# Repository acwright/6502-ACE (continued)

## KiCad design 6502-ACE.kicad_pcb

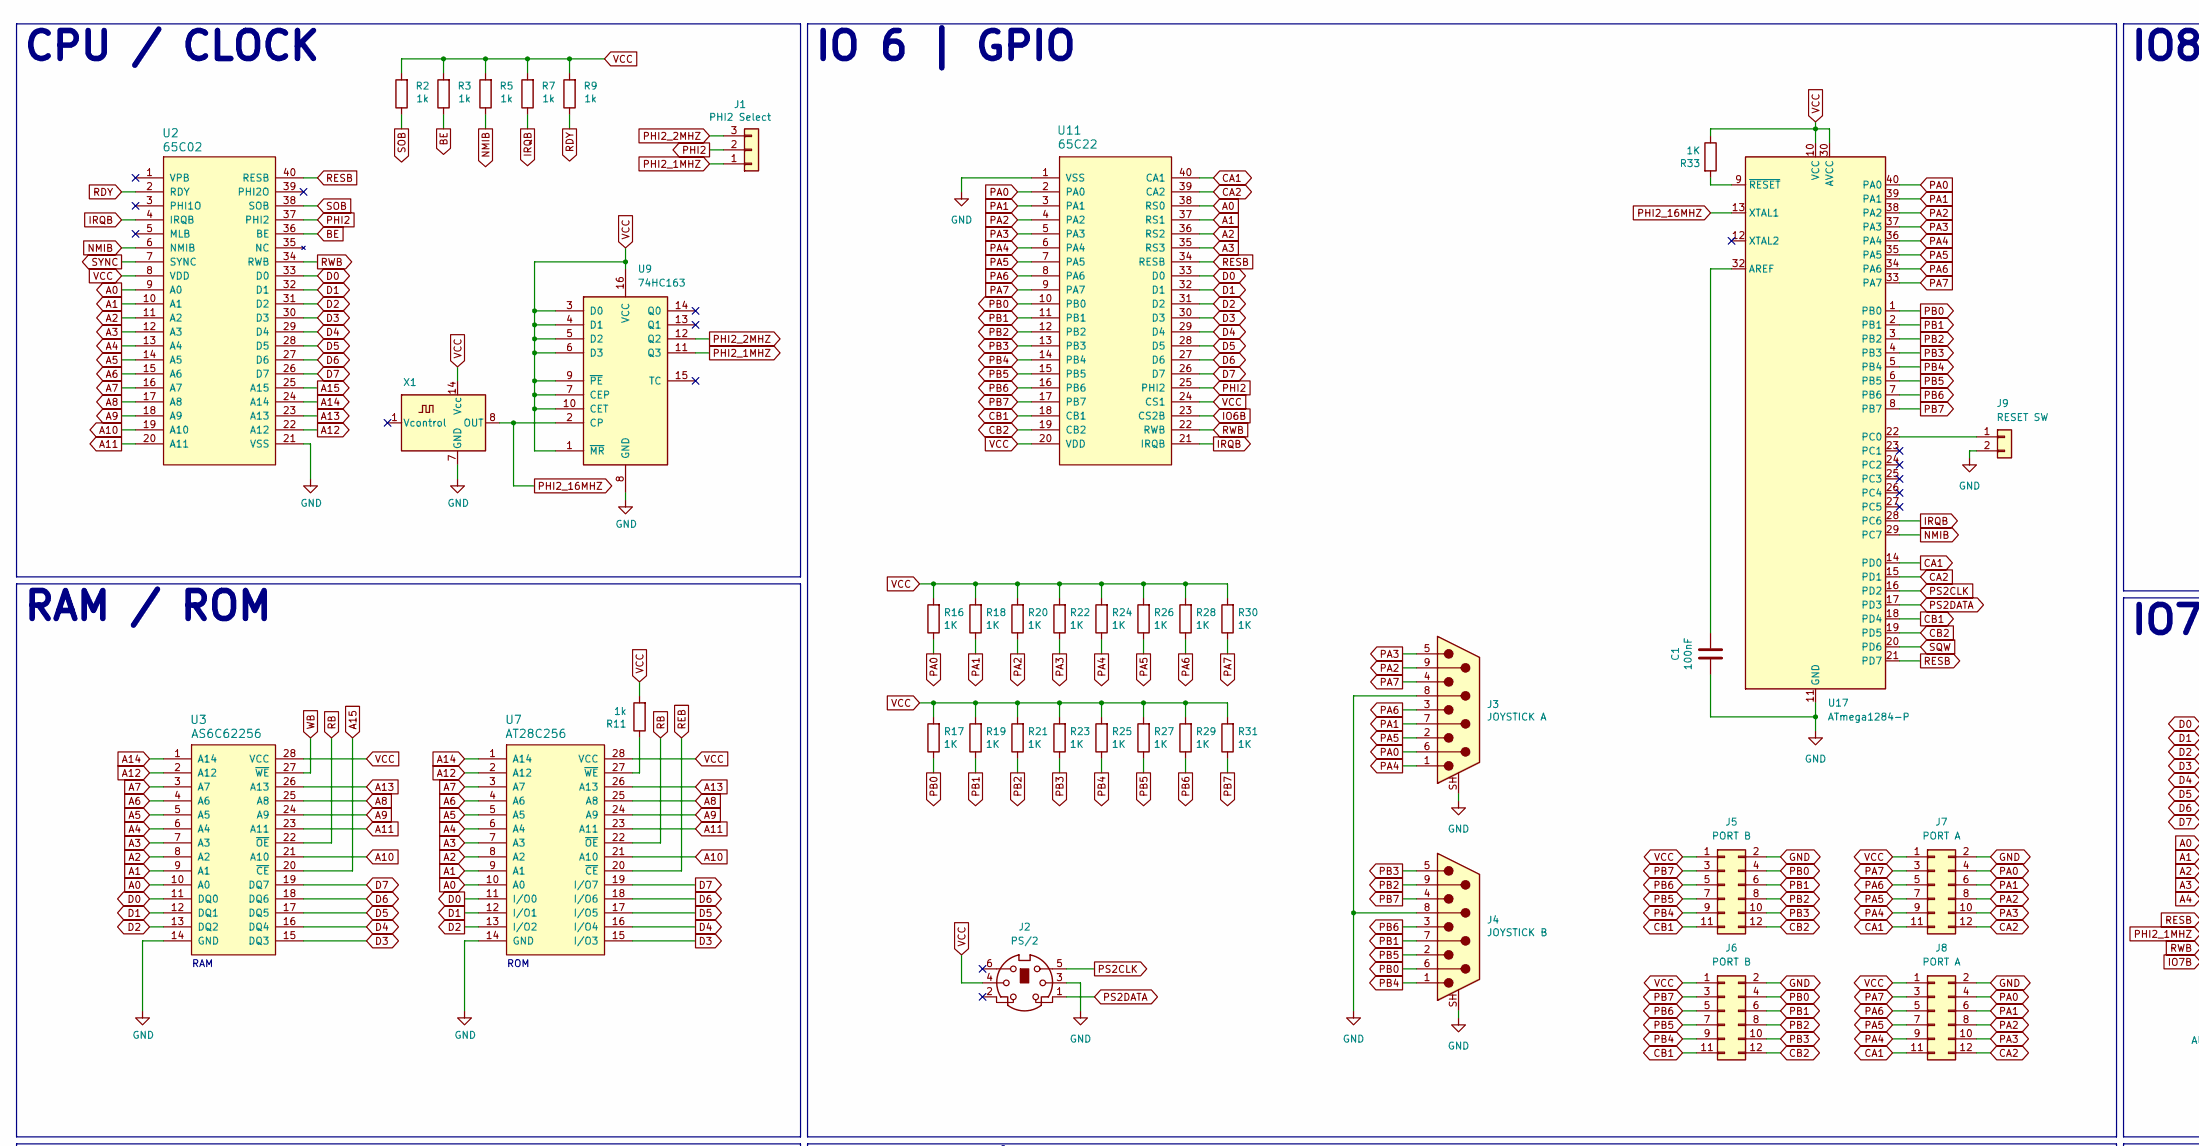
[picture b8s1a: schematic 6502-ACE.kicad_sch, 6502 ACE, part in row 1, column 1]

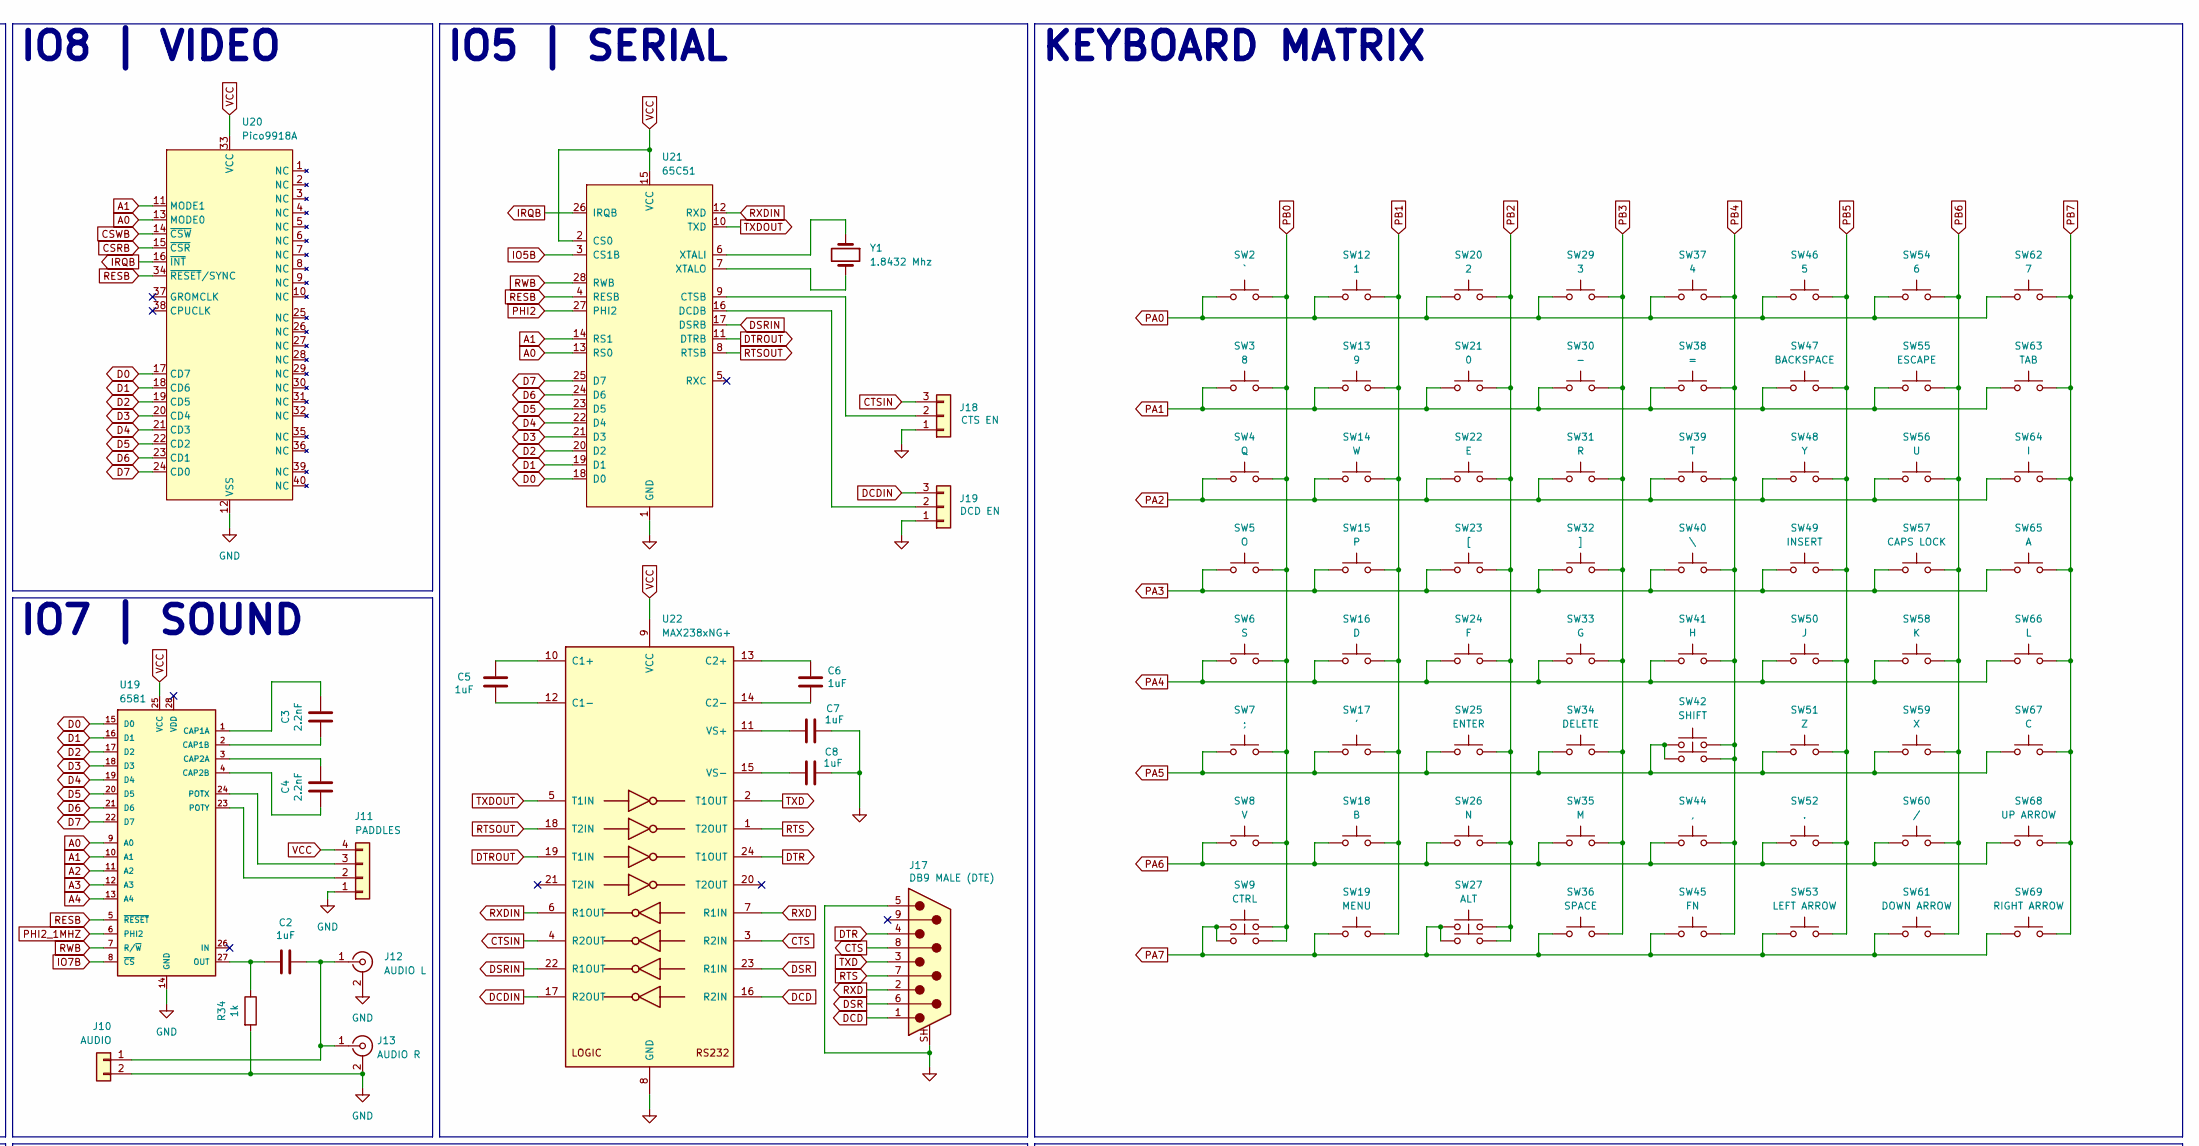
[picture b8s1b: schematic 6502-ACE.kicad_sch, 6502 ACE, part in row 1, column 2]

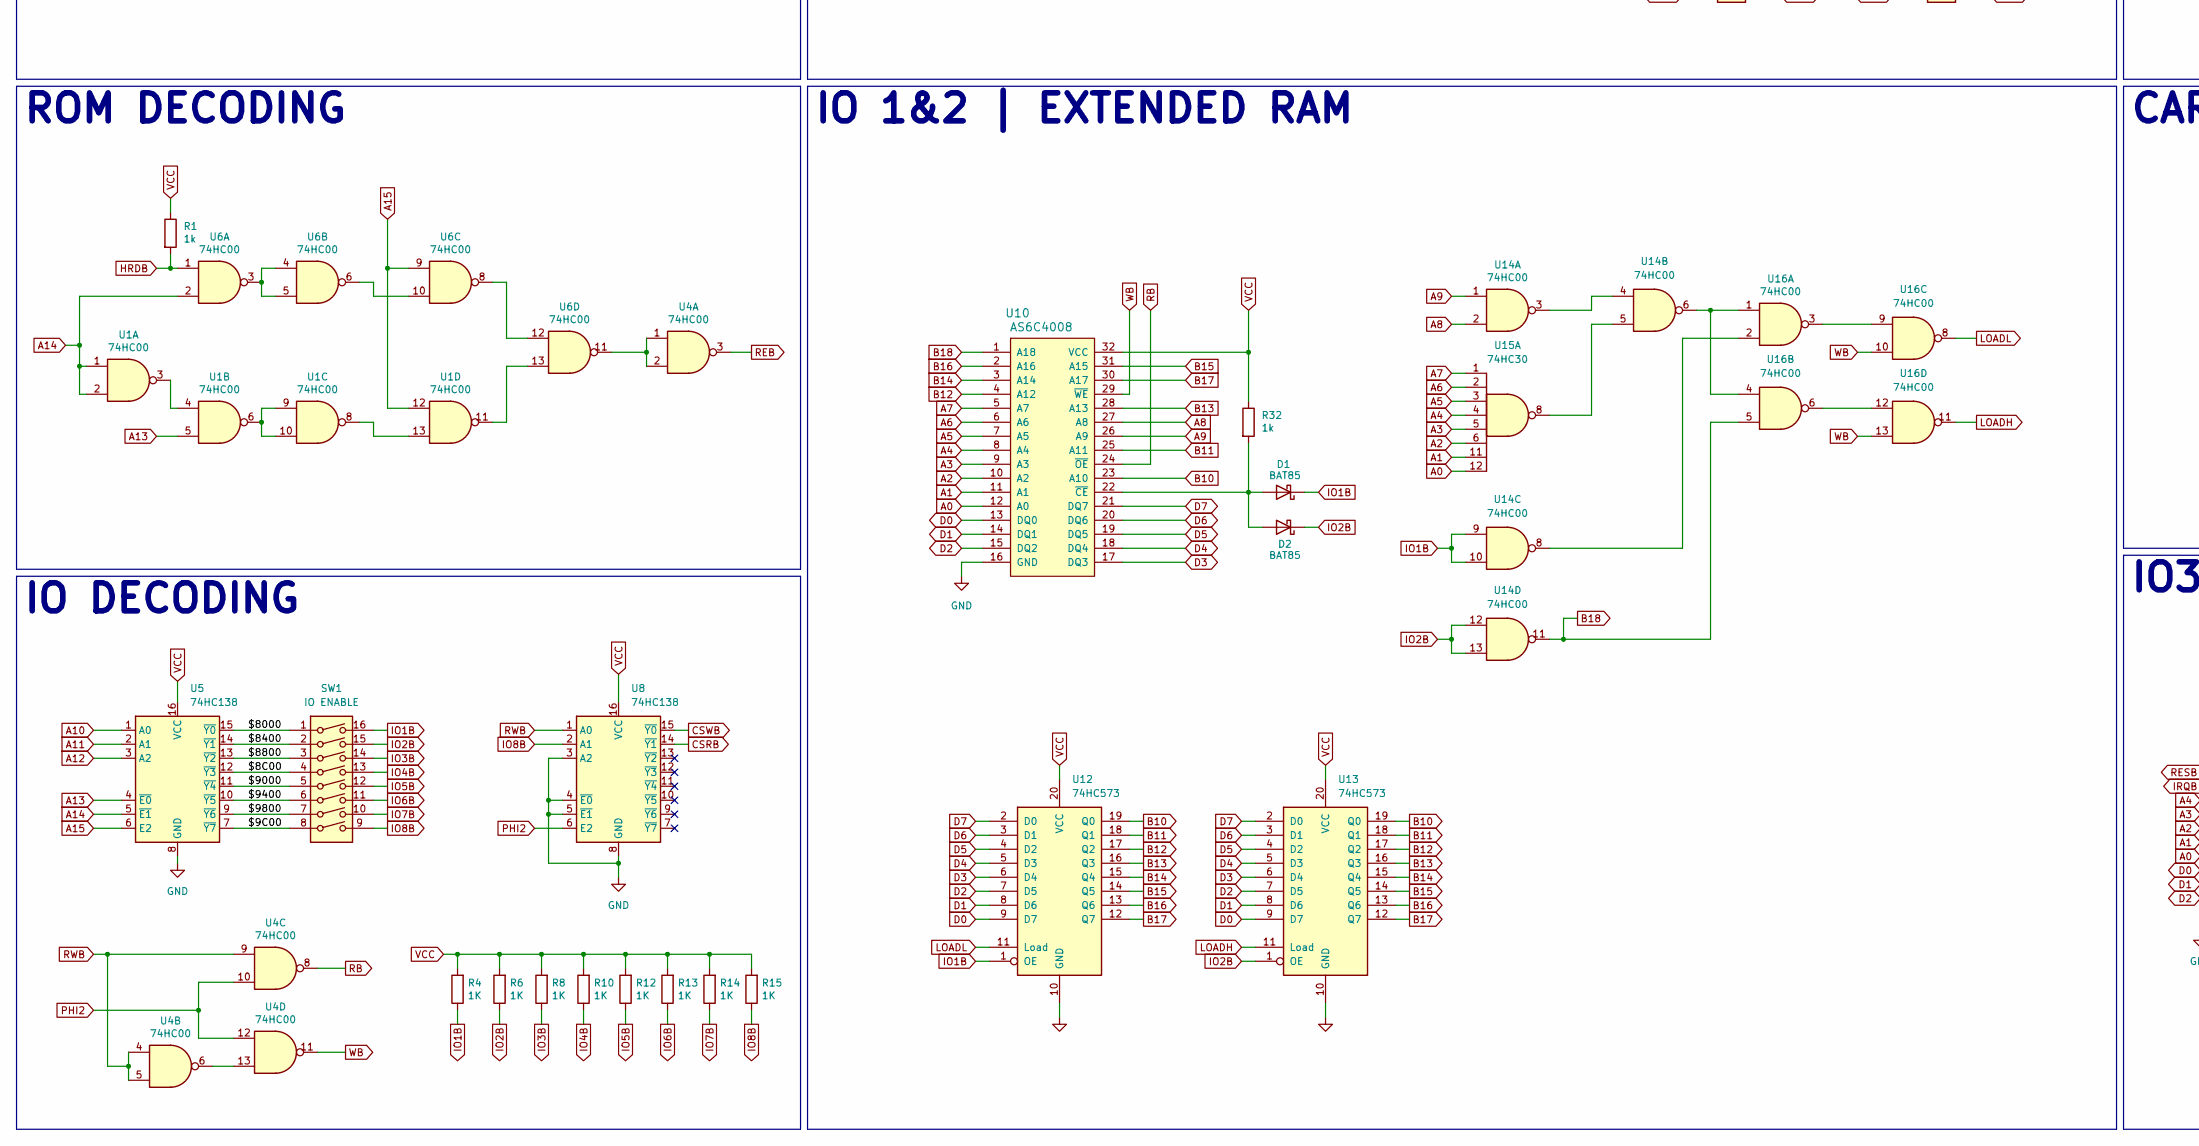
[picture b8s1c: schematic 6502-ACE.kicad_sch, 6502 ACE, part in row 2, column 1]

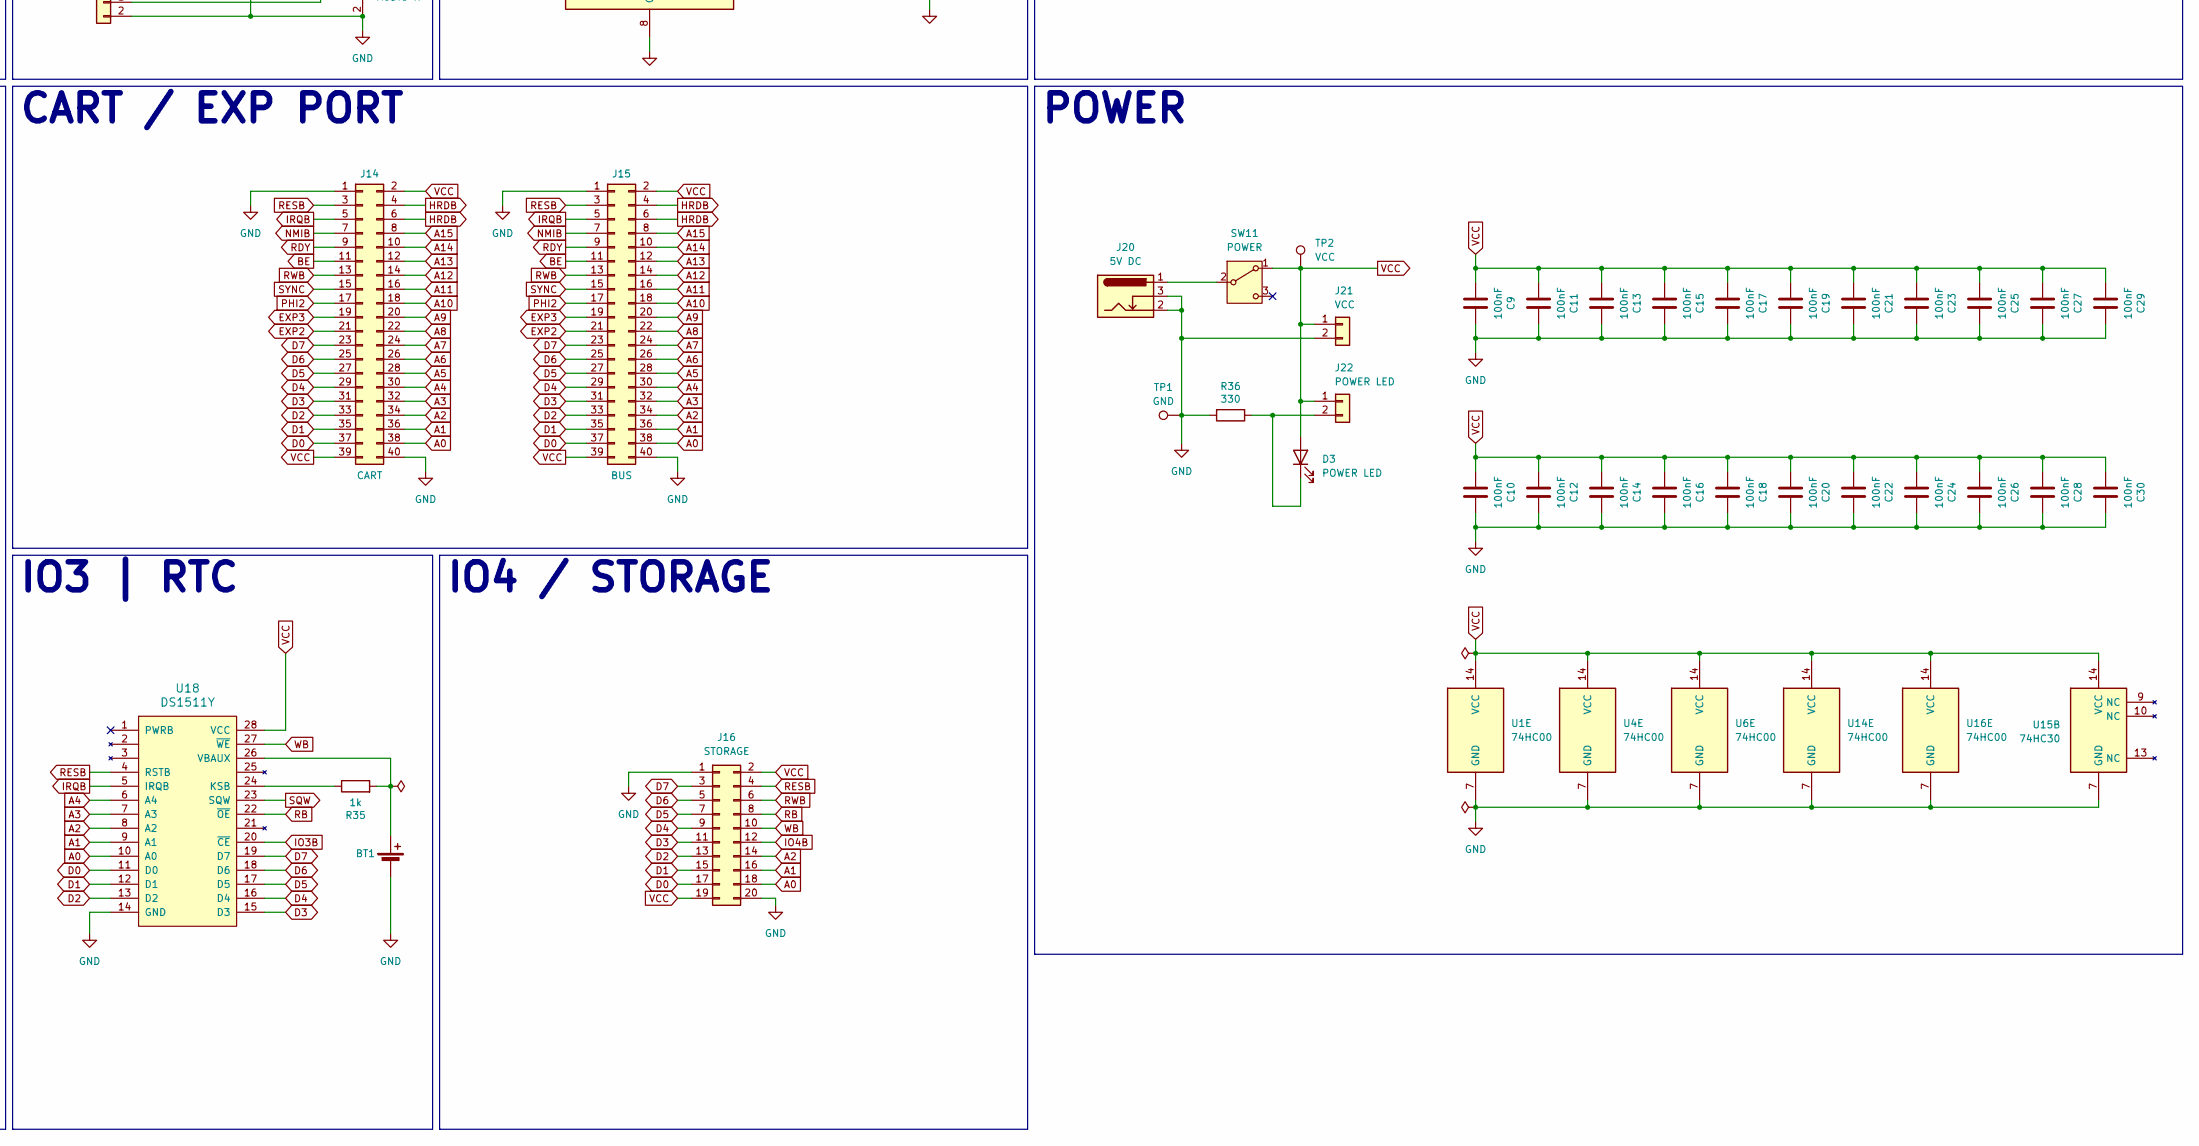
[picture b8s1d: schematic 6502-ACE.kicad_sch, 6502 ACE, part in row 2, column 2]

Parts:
BT1: BAT-HLD-001-THM; BAT_BAT-HLD-001-THM; MPN BAT-HLD-001-THM; Digikey BAT-HLD-001-THM-ND
C1, C9, C10, C11, C12, C13, C14, C15, C16, C17, C18, C19, C20, C21, C22, C23, C24, C25, C26, C27, C28, C29, C30: 100nF; C_Disc_D5.0mm_W2.5mm_P2.50mm
C2, C5, C6, C7, C8: 1uF; C_Disc_D5.0mm_W2.5mm_P2.50mm
C3, C4: 2.2nF; C_Disc_D5.0mm_W2.5mm_P2.50mm
D1, D2: BAT85; D_DO-35_SOD27_P7.62mm_Horizontal; Digikey BAT85SCT-ND
D3: POWER LED; LED_D3.0mm
J1: PHI2 Select; PinHeader_1x03_P2.54mm_Vertical
J2: PS/2; KMDGX-6S-BS
J3: JOYSTICK A; DSUB-9_Pins_Horizontal_P2.77x2.84mm_EdgePinOffset7.70mm_Hou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; MPN D09P33E4GX00LF; Digikey 609-1481-ND
J4: JOYSTICK B; DSUB-9_Pins_Horizontal_P2.77x2.84mm_EdgePinOffset7.70mm_Hou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; MPN D09P33E4GX00LF; Digikey 609-1481-ND
J5, J6: PORT B; 6502 GPIO Connector
J7, J8: PORT A; 6502 GPIO Connector
J9: RESET SW; JST_XH_B2B-XH-A_1x02_P2.50mm_Vertical
J10: AUDIO; JST_XH_B2B-XH-A_1x02_P2.50mm_Vertical
J11: PADDLES; PinHeader_1x04_P2.54mm_Vertical
J12: AUDIO L; SWITCHCRAFT_PJRAN1X1U0XX; Digikey PJRAN1X1U02X-ND
J13: AUDIO R; SWITCHCRAFT_PJRAN1X1U0XX; Digikey PJRAN1X1U03X-ND
J14: CART; RHDR40W82P485X254_2X20_5740X93; Digikey A31723-ND
J15: BUS; 6502 Bus Connector
J16: STORAGE; PinHeader_2x10_P2.54mm_Vertical
J17: DB9 MALE (DTE); DSUB-9_Pins_Horizontal_P2.77x2.84mm_EdgePinOffset7.70mm_Hou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; MPN D09P33E4GX00LF; Digikey 609-1481-ND
J18: CTS EN; PinHeader_1x03_P2.54mm_Vertical
J19: DCD EN; PinHeader_1x03_P2.54mm_Vertical
J20: 5V DC; BarrelJack_Horizontal; Digikey 2073-DCJ200-10-A-K1-K-ND
J21: VCC; JST_XH_B2B-XH-A_1x02_P2.50mm_Vertical
J22: POWER LED; JST_XH_B2B-XH-A_1x02_P2.50mm_Vertical
R1, R2, R3, R5, R7, R9, R11, R32, R34, R35: 1k; R_Axial_DIN0204_L3.6mm_D1.6mm_P5.08mm_Horizontal
R4, R6, R8, R10, R12, R13, R14, R15, R16, R17, R18, R19, R20, R21, R22, R23, R24, R25, R26, R27, R28, R29, R30, R31, R33: 1K; R_Axial_DIN0204_L3.6mm_D1.6mm_P5.08mm_Horizontal
R36: 330; R_Axial_DIN0204_L3.6mm_D1.6mm_P5.08mm_Horizontal
SW1: IO ENABLE; SW_DIP_SPSTx08_Slide_9.78x22.5mm_W7.62mm_P2.54mm
SW2: `; SW_Cherry_MX_1.00u_PCB
SW3: 8; SW_Cherry_MX_1.00u_PCB
SW4: Q; SW_Cherry_MX_1.00u_PCB
SW5: O; SW_Cherry_MX_1.00u_PCB
SW6: S; SW_Cherry_MX_1.00u_PCB
SW7: ;; SW_Cherry_MX_1.00u_PCB
SW8: V; SW_Cherry_MX_1.00u_PCB
SW9: CTRL; SW_Cherry_MX_1.25u_PCB
SW10: R CTRL; SW_Cherry_MX_1.25u_PCB
SW11: POWER; SW_400MSP1R6BLKM6QE; Digikey EG4326-ND
SW12: 1; SW_Cherry_MX_1.00u_PCB
SW13: 9; SW_Cherry_MX_1.00u_PCB
SW14: W; SW_Cherry_MX_1.00u_PCB
SW15: P; SW_Cherry_MX_1.00u_PCB
SW16: D; SW_Cherry_MX_1.00u_PCB
SW17: '; SW_Cherry_MX_1.00u_PCB
SW18: B; SW_Cherry_MX_1.00u_PCB
SW19: MENU; SW_Cherry_MX_1.00u_PCB
SW20: 2; SW_Cherry_MX_1.00u_PCB
SW21: 0; SW_Cherry_MX_1.00u_PCB
SW22: E; SW_Cherry_MX_1.00u_PCB
SW23: [; SW_Cherry_MX_1.00u_PCB
SW24: F; SW_Cherry_MX_1.00u_PCB
SW25: ENTER; SW_Cherry_MX_2.25u_PCB
SW26: N; SW_Cherry_MX_1.00u_PCB
SW27: ALT; SW_Cherry_MX_1.25u_PCB
SW28: R ALT; SW_Cherry_MX_1.25u_PCB
SW29: 3; SW_Cherry_MX_1.00u_PCB
SW30: -; SW_Cherry_MX_1.00u_PCB
SW31: R; SW_Cherry_MX_1.00u_PCB
SW32: ]; SW_Cherry_MX_1.00u_PCB
SW33: G; SW_Cherry_MX_1.00u_PCB
SW34: DELETE; SW_Cherry_MX_1.00u_PCB
SW35: M; SW_Cherry_MX_1.00u_PCB
SW36: SPACE; SW_Cherry_MX_6.25u_PCB
SW37: 4; SW_Cherry_MX_1.00u_PCB
SW38: =; SW_Cherry_MX_1.00u_PCB
SW39: T; SW_Cherry_MX_1.00u_PCB
SW40: \; SW_Cherry_MX_1.50u_PCB
SW41: H; SW_Cherry_MX_1.00u_PCB
SW42: SHIFT; SW_Cherry_MX_2.25u_PCB
SW43: R SHIFT; SW_Cherry_MX_2.25u_PCB
SW44: ,; SW_Cherry_MX_1.00u_PCB
SW45: FN; SW_Cherry_MX_1.25u_PCB
SW46: 5; SW_Cherry_MX_1.00u_PCB
SW47: BACKSPACE; SW_Cherry_MX_2.00u_PCB
SW48: Y; SW_Cherry_MX_1.00u_PCB
SW49: INSERT; SW_Cherry_MX_1.00u_PCB
SW50: J; SW_Cherry_MX_1.00u_PCB
SW51: Z; SW_Cherry_MX_1.00u_PCB
SW52: .; SW_Cherry_MX_1.00u_PCB
SW53: LEFT ARROW; SW_Cherry_MX_1.00u_PCB
SW54: 6; SW_Cherry_MX_1.00u_PCB
SW55: ESCAPE; SW_Cherry_MX_1.00u_PCB
SW56: U; SW_Cherry_MX_1.00u_PCB
SW57: CAPS LOCK; SW_Cherry_MX_1.75u_PCB
SW58: K; SW_Cherry_MX_1.00u_PCB
SW59: X; SW_Cherry_MX_1.00u_PCB
SW60: /; SW_Cherry_MX_1.00u_PCB
SW61: DOWN ARROW; SW_Cherry_MX_1.00u_PCB
SW62: 7; SW_Cherry_MX_1.00u_PCB
SW63: TAB; SW_Cherry_MX_1.50u_PCB
SW64: I; SW_Cherry_MX_1.00u_PCB
SW65: A; SW_Cherry_MX_1.00u_PCB
SW66: L; SW_Cherry_MX_1.00u_PCB
SW67: C; SW_Cherry_MX_1.00u_PCB
SW68: UP ARROW; SW_Cherry_MX_1.00u_PCB
SW69: RIGHT ARROW; SW_Cherry_MX_1.00u_PCB
TP1: GND; TestPoint_Pad_2.5x2.5mm
TP2: VCC; TestPoint_Pad_2.5x2.5mm
U1, U4, U6, U14, U16: 74HC00; DIP-14_W7.62mm_Socket_LongPads; Digikey 296-1563-5-ND
U2: 65C02; DIP-40_W15.24mm_Socket_LongPads; Mouser 955-W65C02S6TPG-14
U3: AS6C62256; DIP-28_W15.24mm_Socket_LongPads; Digikey 1450-1033-ND
U5, U8: 74HC138; DIP-16_W7.62mm_Socket_LongPads; Digikey 296-1575-5-ND
U7: AT28C256; DIP_Socket-28_W11.9mm_W12.7mm_W15.24mm_W17.78mm_W18.5mm_3M_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; Digikey AT28C256-15PU-ND
U9: 74HC163; DIP-16_W7.62mm_Socket_LongPads; Digikey 296-8246-5-ND
U10: AS6C4008; DIP-32_W15.24mm_Socket_LongPads; Digikey 1450-1027-ND
U11: 65C22; DIP-40_W15.24mm_Socket_LongPads; Mouser 955-W65C22N6TPG-14
U12, U13: 74HC573; DIP-20_W7.62mm_Socket_LongPads; Digikey 296-12815-5-ND
U15: 74HC30; DIP-14_W7.62mm_Socket_LongPads; Digikey 296-9196-5-ND
U17: ATmega1284-P; DIP-40_W15.24mm; Digikey ATMEGA1284-PU-ND
U18: DS1511Y; DIP-28_W15.24mm_Socket_LongPads; Digikey DS1511Y+-ND
U19: 6581; DIP-28_W15.24mm_Socket_LongPads
U20: Pico9918A; DIP-40_W15.24mm_LongPads
U21: 65C51; DIP-28_W15.24mm_Socket_LongPads
U22: MAX238xNG+; DIP-24_W7.62mm; Digikey MAX238CNG+-ND
X1: OCXO-14; Oscillator_DIP-14; Digikey X947-ND
Y1: 1.8432 Mhz; Crystal_HC49-U_Vertical; Digikey 3155-1.8432M20P2/49U-ND

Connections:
/$8C00: SW1.4, U5.12 (~Y3)
/$9C00: SW1.8, U5.7 (~Y7)
/$8000: SW1.1, U5.15 (~Y0)
/$8400: SW1.2, U5.14 (~Y1)
/$8800: SW1.3, U5.13 (~Y2)
/$9000: SW1.5, U5.11 (~Y4)
/$9400: SW1.6, U5.10 (~Y5)
/$9800: SW1.7, U5.9 (~Y6)
A0: J14.38, J15.38, J16.18, U2.9 (A0), U3.10 (A0), U7.10 (A0), U10.12 (A0), U11.38 (RS0), U15.12, U18.10 (A0), U19.9 (A0), U20.13 (MODE0), U21.13 (RS0)
A1: J14.36, J15.36, J16.16, U2.10 (A1), U3.9 (A1), U7.9 (A1), U10.11 (A1), U11.37 (RS1), U15.11, U18.9 (A1), U19.10 (A1), U20.11 (MODE1), U21.14 (RS1)
A2: J14.34, J15.34, J16.14, U2.11 (A2), U3.8 (A2), U7.8 (A2), U10.10 (A2), U11.36 (RS2), U15.6, U18.8 (A2), U19.11 (A2)
A3: J14.32, J15.32, U2.12 (A3), U3.7 (A3), U7.7 (A3), U10.9 (A3), U11.35 (RS3), U15.5, U18.7 (A3), U19.12 (A3)
A4: J14.30, J15.30, U2.13 (A4), U3.6 (A4), U7.6 (A4), U10.8 (A4), U15.4, U18.6 (A4), U19.13 (A4)
A5: J14.28, J15.28, U2.14 (A5), U3.5 (A5), U7.5 (A5), U10.7 (A5), U15.3
A6: J14.26, J15.26, U2.15 (A6), U3.4 (A6), U7.4 (A6), U10.6 (A6), U15.2
A7: J14.24, J15.24, U2.16 (A7), U3.3 (A7), U7.3 (A7), U10.5 (A7), U15.1
A8: J14.22, J15.22, U2.17 (A8), U3.25 (A8), U7.25 (A8), U10.27 (A8), U14.2
A9: J14.20, J15.20, U2.18 (A9), U3.24 (A9), U7.24 (A9), U10.26 (A9), U14.1
A10: J14.18, J15.18, U2.19 (A10), U3.21 (A10), U5.1 (A0), U7.21 (A10)
A11: J14.16, J15.16, U2.20 (A11), U3.23 (A11), U5.2 (A1), U7.23 (A11)
A12: J14.14, J15.14, U2.22 (A12), U3.2 (A12), U5.3 (A2), U7.2 (A12)
A13: J14.12, J15.12, U1.5, U2.23 (A13), U3.26 (A13), U5.4 (~E0), U7.26 (A13)
A14: J14.10, J15.10, U1.1, U1.2, U2.24 (A14), U3.1 (A14), U5.5 (~E1), U6.2, U7.1 (A14)
A15: J14.8, J15.8, U1.12, U2.25 (A15), U3.20 (~CE), U5.6 (E2), U6.9
B10: U10.23 (A10), U12.19 (Q0), U13.19 (Q0)
B11: U10.25 (A11), U12.18 (Q1), U13.18 (Q1)
B12: U10.4 (A12), U12.17 (Q2), U13.17 (Q2)
B13: U10.28 (A13), U12.16 (Q3), U13.16 (Q3)
B14: U10.3 (A14), U12.15 (Q4), U13.15 (Q4)
B15: U10.31 (A15), U12.14 (Q5), U13.14 (Q5)
B16: U10.2 (A16), U12.13 (Q6), U13.13 (Q6)
B17: U10.30 (A17), U12.12 (Q7), U13.12 (Q7)
B18: U10.1 (A18), U14.11, U16.5
BE: J14.11, J15.11, R3.1, U2.36 (BE)
CA1: J7.11, J8.11, U11.40 (CA1), U17.14 (PD0)
CA2: J7.12, J8.12, U11.39 (CA2), U17.15 (PD1)
CB1: J5.11, J6.11, U11.18 (CB1), U17.18 (PD4)
CB2: J5.12, J6.12, U11.19 (CB2), U17.19 (PD5)
CSRB: U8.14 (~Y1), U20.15 (~CSR)
CSWB: U8.15 (~Y0), U20.14 (~CSW)
CTS: J17.8, U22.3 (R2IN)
CTSIN: J18.3, U22.4 (R2OUT)
D0: J14.37, J15.37, J16.17, U2.33 (D0), U3.11 (DQ0), U7.11 (I/O0), U10.13 (DQ0), U11.33 (D0), U12.9 (D7), U13.9 (D7), U18.11 (D0), U19.15 (D0), U20.17 (CD7), U21.18 (D0)
D1: J14.35, J15.35, J16.15, U2.32 (D1), U3.12 (DQ1), U7.12 (I/O1), U10.14 (DQ1), U11.32 (D1), U12.8 (D6), U13.8 (D6), U18.12 (D1), U19.16 (D1), U20.18 (CD6), U21.19 (D1)
D2: J14.33, J15.33, J16.13, U2.31 (D2), U3.13 (DQ2), U7.13 (I/O2), U10.15 (DQ2), U11.31 (D2), U12.7 (D5), U13.7 (D5), U18.13 (D2), U19.17 (D2), U20.19 (CD5), U21.20 (D2)
D3: J14.31, J15.31, J16.11, U2.30 (D3), U3.15 (DQ3), U7.15 (I/O3), U10.17 (DQ3), U11.30 (D3), U12.6 (D4), U13.6 (D4), U18.15 (D3), U19.18 (D3), U20.20 (CD4), U21.21 (D3)
D4: J14.29, J15.29, J16.9, U2.29 (D4), U3.16 (DQ4), U7.16 (I/O4), U10.18 (DQ4), U11.29 (D4), U12.5 (D3), U13.5 (D3), U18.16 (D4), U19.19 (D4), U20.21 (CD3), U21.22 (D4)
D5: J14.27, J15.27, J16.7, U2.28 (D5), U3.17 (DQ5), U7.17 (I/O5), U10.19 (DQ5), U11.28 (D5), U12.4 (D2), U13.4 (D2), U18.17 (D5), U19.20 (D5), U20.22 (CD2), U21.23 (D5)
D6: J14.25, J15.25, J16.5, U2.27 (D6), U3.18 (DQ6), U7.18 (I/O6), U10.20 (DQ6), U11.27 (D6), U12.3 (D1), U13.3 (D1), U18.18 (D6), U19.21 (D6), U20.23 (CD1), U21.24 (D6)
D7: J14.23, J15.23, J16.3, U2.26 (D7), U3.19 (DQ7), U7.19 (I/O7), U10.21 (DQ7), U11.26 (D7), U12.2 (D0), U13.2 (D0), U18.19 (D7), U19.22 (D7), U20.24 (CD0), U21.25 (D7)
DCD: J17.1, U22.16 (R2IN)
DCDIN: J19.3, U22.17 (R2OUT)
DSR: J17.6, U22.23 (R1IN)
DSRIN: U21.17 (DSRB), U22.22 (R1OUT)
DTR: J17.4, U22.24 (T1OUT)
DTROUT: U21.11 (DTRB), U22.19 (T1IN)
EXP2: J14.21, J15.21
EXP3: J14.19, J15.19
GND: BT1.2 (-), C1.1, C7.2, C8.2, C9.2, C10.2, C11.2, C12.2, C13.2, C14.2, C15.2, C16.2, C17.2, C18.2, C19.2, C20.2, C21.2, C22.2, C23.2, C24.2, C25.2, C26.2, C27.2, C28.2, C29.2, C30.2, J2.3, J3.8, J3.SH (PAD), J4.8, J4.SH (PAD), J5.2, J6.2, J7.2, J8.2, J9.2, J10.2, J11.1, J12.2 (Ext), J13.2 (Ext), J14.1, J14.40, J15.1, J15.40, J16.1, J16.20, J17.5, J17.SH (PAD), J18.1, J19.1, J20.2, J20.3, J21.2, R34.2, R36.2, TP1.1 (1_1), U1.7 (GND), U2.21 (VSS), U3.14 (GND), U4.7 (GND), U5.8 (GND), U6.7 (GND), U7.14 (GND), U8.3 (A2), U8.4 (~E0), U8.5 (~E1), U8.8 (GND), U9.8 (GND), U10.16 (GND), U11.1 (VSS), U12.10 (GND), U13.10 (GND), U14.7 (GND), U15.7 (GND), U16.7 (GND), U17.11 (GND), U17.31 (GND), U18.14 (GND), U19.14 (GND), U20.12 (VSS), U21.1 (GND), U22.8 (GND), X1.7 (GND)
HRDB: J14.4, J14.6, J15.4, J15.6, R1.2, U6.1
IO1B: D1.1 (K), R4.1, SW1.16, U12.1 (OE), U14.9, U14.10
IO2B: D2.1 (K), R6.1, SW1.15, U13.1 (OE), U14.12, U14.13
IO3B: R8.1, SW1.14, U18.20 (~CE)
IO4B: J16.12, R10.1, SW1.13
IO5B: R12.1, SW1.12, U21.3 (CS1B)
IO6B: R13.1, SW1.11, U11.23 (CS2B)
IO7B: R14.1, SW1.10, U19.8 (~CS)
IO8B: R15.1, SW1.9, U8.2 (A1)
IRQB: J14.5, J15.5, R7.1, U2.4 (IRQB), U11.21 (IRQB), U17.28 (PC6), U18.5 (IRQB), U20.16 (~INT), U21.26 (IRQB)
LOADH: U13.11 (Load), U16.11
LOADL: U12.11 (Load), U16.8
NMIB: J14.7, J15.7, R5.1, U2.6 (NMIB), U17.29 (PC7)
unnamed: BT1.1 (+), R35.2, U18.26 (VBAUX)
unnamed: D1.2 (A), D2.2 (A), R32.2, U10.22 (~CE)
unnamed: D3.1 (K), J22.2, R36.1
unnamed: J9.1, U17.22 (PC0)
unnamed: C2.2, J10.1, J12.1 (In), J13.1 (In)
unnamed: J11.2, U19.23 (POTY)
unnamed: J11.3, U19.24 (POTX)
unnamed: J18.2, U21.9 (CTSB)
unnamed: J19.2, U21.16 (DCDB)
unnamed: J20.1, SW11.2 (B)
unnamed: U1.3, U1.4
unnamed: U1.6, U1.9, U1.10
unnamed: U1.11, U6.13
unnamed: U1.8, U1.13
unnamed: U4.1, U4.2, U6.11
unnamed: U4.6, U4.13
unnamed: U6.3, U6.4, U6.5
unnamed: U6.6, U6.10
unnamed: U6.8, U6.12
unnamed: R11.1, U7.27 (~WE)
unnamed: U14.3, U14.4
unnamed: U14.5, U15.8
unnamed: U14.6, U16.1, U16.4
unnamed: U14.8, U16.2
unnamed: U16.3, U16.9
unnamed: U16.6, U16.12
unnamed: C1.2, U17.32 (AREF)
unnamed: R33.2, U17.9 (~RESET)
unnamed: R35.1, U18.24 (KSB)
unnamed: C3.2, U19.1 (CAP1A)
unnamed: C3.1, U19.2 (CAP1B)
unnamed: C4.2, U19.3 (CAP2A)
unnamed: C4.1, U19.4 (CAP2B)
unnamed: C2.1, R34.1, U19.27 (OUT)
unnamed: U21.6 (XTALI), Y1.1
unnamed: U21.7 (XTALO), Y1.2
unnamed: C5.1, U22.10 (C1+)
unnamed: C5.2, U22.12 (C1-)
unnamed: C6.1, U22.13 (C2+)
unnamed: C6.2, U22.14 (C2-)
unnamed: C7.1, U22.11 (VS+)
unnamed: C8.1, U22.15 (VS-)
PA0: J3.6, J7.4, J8.4, R16.1, SW2.1, SW12.1, SW20.1, SW29.1, SW37.1, SW46.1, SW54.1, SW62.1, U11.2 (PA0), U17.40 (PA0)
PA1: J3.7, J7.6, J8.6, R18.1, SW3.1, SW13.1, SW21.1, SW30.1, SW38.1, SW47.1, SW55.1, SW63.1, U11.3 (PA1), U17.39 (PA1)
PA2: J3.9, J7.8, J8.8, R20.1, SW4.1, SW14.1, SW22.1, SW31.1, SW39.1, SW48.1, SW56.1, SW64.1, U11.4 (PA2), U17.38 (PA2)
PA3: J3.5, J7.10, J8.10, R22.1, SW5.1, SW15.1, SW23.1, SW32.1, SW40.1, SW49.1, SW57.1, SW65.1, U11.5 (PA3), U17.37 (PA3)
PA4: J3.1, J7.9, J8.9, R24.1, SW6.1, SW16.1, SW24.1, SW33.1, SW41.1, SW50.1, SW58.1, SW66.1, U11.6 (PA4), U17.36 (PA4)
PA5: J3.2, J7.7, J8.7, R26.1, SW7.1, SW17.1, SW25.1, SW34.1, SW42.1, SW43.1, SW51.1, SW59.1, SW67.1, U11.7 (PA5), U17.35 (PA5)
PA6: J3.3, J7.5, J8.5, R28.1, SW8.1, SW18.1, SW26.1, SW35.1, SW44.1, SW52.1, SW60.1, SW68.1, U11.8 (PA6), U17.34 (PA6)
PA7: J3.4, J7.3, J8.3, R30.1, SW9.1, SW10.1, SW19.1, SW27.1, SW28.1, SW36.1, SW45.1, SW53.1, SW61.1, SW69.1, U11.9 (PA7), U17.33 (PA7)
PB0: J4.6, J5.4, J6.4, R17.1, SW2.2, SW3.2, SW4.2, SW5.2, SW6.2, SW7.2, SW8.2, SW9.2, SW10.2, U11.10 (PB0), U17.1 (PB0)
PB1: J4.7, J5.6, J6.6, R19.1, SW12.2, SW13.2, SW14.2, SW15.2, SW16.2, SW17.2, SW18.2, SW19.2, U11.11 (PB1), U17.2 (PB1)
PB2: J4.9, J5.8, J6.8, R21.1, SW20.2, SW21.2, SW22.2, SW23.2, SW24.2, SW25.2, SW26.2, SW27.2, SW28.2, U11.12 (PB2), U17.3 (PB2)
PB3: J4.5, J5.10, J6.10, R23.1, SW29.2, SW30.2, SW31.2, SW32.2, SW33.2, SW34.2, SW35.2, SW36.2, U11.13 (PB3), U17.4 (PB3)
PB4: J4.1, J5.9, J6.9, R25.1, SW37.2, SW38.2, SW39.2, SW40.2, SW41.2, SW42.2, SW43.2, SW44.2, SW45.2, U11.14 (PB4), U17.5 (PB4)
PB5: J4.2, J5.7, J6.7, R27.1, SW46.2, SW47.2, SW48.2, SW49.2, SW50.2, SW51.2, SW52.2, SW53.2, U11.15 (PB5), U17.6 (PB5)
PB6: J4.3, J5.5, J6.5, R29.1, SW54.2, SW55.2, SW56.2, SW57.2, SW58.2, SW59.2, SW60.2, SW61.2, U11.16 (PB6), U17.7 (PB6)
PB7: J4.4, J5.3, J6.3, R31.1, SW62.2, SW63.2, SW64.2, SW65.2, SW66.2, SW67.2, SW68.2, SW69.2, U11.17 (PB7), U17.8 (PB7)
PHI2: J1.2, J14.17, J15.17, U2.37 (PHI2), U4.10, U4.12, U8.6 (E2), U11.25 (PHI2), U21.27 (PHI2)
PHI2_1MHZ: J1.1, U9.11 (Q3), U19.6 (PHI2)
PHI2_2MHZ: J1.3, U9.12 (Q2)
PHI2_16MHZ: U9.2 (CP), U17.13 (XTAL1), X1.8 (OUT)
PS2CLK: J2.5, U17.16 (PD2)
PS2DATA: J2.1, U17.17 (PD3)
RB: J16.8, U3.22 (~OE), U4.8, U7.22 (~OE), U10.24 (~OE), U18.22 (~OE)
RDY: J14.9, J15.9, R9.1, U2.2 (RDY)
REB: U4.3, U7.20 (~CE)
RESB: J14.3, J15.3, J16.4, U2.40 (RESB), U11.34 (RESB), U17.21 (PD7), U18.4 (RSTB), U19.5 (~RESET), U20.34 (~RESET/SYNC), U21.4 (RESB)
RTS: J17.7, U22.1 (T2OUT)
RTSOUT: U21.8 (RTSB), U22.18 (T2IN)
RWB: J14.13, J15.13, J16.6, U2.34 (RWB), U4.4, U4.5, U4.9, U8.1 (A0), U11.22 (RWB), U19.7 (R/~W), U21.28 (RWB)
RXD: J17.2, U22.7 (R1IN)
RXDIN: U21.12 (RXD), U22.6 (R1OUT)
SOB: R2.1, U2.38 (SOB)
SQW: U17.20 (PD6), U18.23 (SQW)
SYNC: J14.15, J15.15, U2.7 (SYNC)
TXD: J17.3, U22.2 (T1OUT)
TXDOUT: U21.10 (TXD), U22.5 (T1IN)
VCC: C9.1, C10.1, C11.1, C12.1, C13.1, C14.1, C15.1, C16.1, C17.1, C18.1, C19.1, C20.1, C21.1, C22.1, C23.1, C24.1, C25.1, C26.1, C27.1, C28.1, C29.1, C30.1, D3.2 (A), J2.4, J5.1, J6.1, J7.1, J8.1, J11.4, J14.2, J14.39, J15.2, J15.39, J16.2, J16.19, J21.1, J22.1, R1.1, R2.2, R3.2, R4.2, R5.2, R6.2, R7.2, R8.2, R9.2, R10.2, R11.2, R12.2, R13.2, R14.2, R15.2, R16.2, R17.2, R18.2, R19.2, R20.2, R21.2, R22.2, R23.2, R24.2, R25.2, R26.2, R27.2, R28.2, R29.2, R30.2, R31.2, R32.1, R33.1, SW11.1 (A), TP2.1 (1_1), U1.14 (VCC), U2.8 (VDD), U3.28 (VCC), U4.14 (VCC), U5.16 (VCC), U6.14 (VCC), U7.28 (VCC), U8.16 (VCC), U9.1 (~MR), U9.3 (D0), U9.4 (D1), U9.5 (D2), U9.6 (D3), U9.7 (CEP), U9.9 (~PE), U9.10 (CET), U9.16 (VCC), U10.32 (VCC), U11.20 (VDD), U11.24 (CS1), U12.20 (VCC), U13.20 (VCC), U14.14 (VCC), U15.14 (VCC), U16.14 (VCC), U17.10 (VCC), U17.30 (AVCC), U18.28 (VCC), U19.25 (VCC), U20.33 (VCC), U21.2 (CS0), U21.15 (VCC), U22.9 (VCC), X1.14 (Vcc)
WB: J16.10, U3.27 (~WE), U4.11, U10.29 (~WE), U16.10, U16.13, U18.27 (~WE)

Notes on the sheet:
ROM
RAM
IO4 / STORAGE
RAM / ROM
POWER
IO7 | SOUND
IO5 | SERIAL
IO8 | VIDEO
ROM DECODING
IO DECODING
IO 6 | GPIO
CART / EXP PORT
IO3 | RTC
CPU / CLOCK
IO 1&2 | EXTENDED RAM
KEYBOARD MATRIX

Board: 2 copper layers, 187 parts (0 on the bottom side), 152 nets, no tracks yet.

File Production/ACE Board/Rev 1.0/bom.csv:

Designator,Footprint,Quantity,Value,LCSC Part #
BT1,BAT_BAT-HLD-001-THM,1,CR2032,BAT-HLD-001-THM
"C1, C10, C11, C12, C13, C14, C15, C16, C17, C18, C19, C20, C21, C22, C23, C24, C25, C26, C27, C28, C29, C30, C9",C_Disc_D5.0mm_W2.5mm_P2.50mm,23,100nF,
"C2, C3, C5, C6, C8",C_Disc_D5.0mm_W2.5mm_P2.50mm,5,1uF,
"C4, C7",C_Disc_D5.0mm_W2.5mm_P2.50mm,2,2.2nF,
D1,LED_D3.0mm,1,POWER LED,
"D2, D3",D_DO-35_SOD27_P7.62mm_Horizontal,2,BAT85,
J1,PinHeader_1x03_P2.54mm_Vertical,1,PHI2 SELECT,
J10,6502 GPIO Connector,1,PORT A,
J11,SWITCHCRAFT_PJRAN1X1U0XX,1,AUDIO L,
J12,DSUB-9_Pins_Horizontal_P2.77x2.84mm_EdgePinOffset7.70mm_Housed_MountingHolesOffset9.12mm,1,DB9 MALE (DTE),D09P33E4GX00LF
J13,KMDGX-6S-BS,1,PS/2,
J14,SWITCHCRAFT_PJRAN1X1U0XX,1,AUDIO R,
J15,PinHeader_1x02_P2.54mm_Vertical,1,AUDIO,
J16,BarrelJack_Horizontal,1,5V DC,
J17,RHDR40W82P485X254_2X20_5740X93,1,CART,
J18,6502 Bus Connector,1,BUS,
J19,PinHeader_1x02_P2.54mm_Vertical,1,VCC,
J2,PinHeader_1x03_P2.54mm_Vertical,1,CTS EN,
J20,PinHeader_1x02_P2.54mm_Vertical,1,POWER LED,
J21,PinSocket_2x10_P2.54mm_Horizontal,1,STORAGE,PPPC102LJBN-RC
J22,PinHeader_1x16_P2.00mm_Vertical,1,KEYBOARD,
J3,PinHeader_1x02_P2.54mm_Vertical,1,RESET SW,
J4,PinHeader_1x03_P2.54mm_Vertical,1,DCD EN,
J5,PinHeader_1x02_P2.54mm_Vertical,1,VDD,
J6,DSUB-9_Pins_Horizontal_P2.77x2.84mm_EdgePinOffset7.70mm_Housed_MountingHolesOffset9.12mm,1,JOYSTICK A,D09P33E4GX00LF
J7,PinHeader_1x04_P2.54mm_Vertical,1,PADDLES,
J8,DSUB-9_Pins_Horizontal_P2.77x2.84mm_EdgePinOffset7.70mm_Housed_MountingHolesOffset9.12mm,1,JOYSTICK B,D09P33E4GX00LF
J9,6502 GPIO Connector,1,PORT B,
"R1, R10, R11, R12, R13, R14, R16, R17, R18, R19, R2, R20, R21, R22, R23, R24, R25, R27, R28, R29, R3, R30, R31, R32, R33, R34, R35, R36, R4, R5, R6, R7, R8, R9",R_Axial_DIN0204_L3.6mm_D1.6mm_P5.08mm_Horizontal,34,1k,
R26,R_Axial_DIN0204_L3.6mm_D1.6mm_P5.08mm_Horizontal,1,330,
SW1,SW_Cherry_MX_1.00u_PCB,1,`,
SW10,SW_Cherry_MX_1.00u_PCB,1,9,
SW11,SW_Cherry_MX_1.00u_PCB,1,0,
SW12,SW_Cherry_MX_1.00u_PCB,1,-,
SW13,SW_Cherry_MX_1.00u_PCB,1,=,
SW14,SW_Cherry_MX_2.00u_PCB,1,BACKSPACE,
SW15,SW_Cherry_MX_1.00u_PCB,1,ESCAPE,
SW16,SW_Cherry_MX_1.50u_PCB,1,TAB,
SW17,SW_Cherry_MX_1.00u_PCB,1,Q,
SW18,SW_Cherry_MX_1.00u_PCB,1,W,
SW19,SW_Cherry_MX_1.00u_PCB,1,E,
SW2,SW_Cherry_MX_1.00u_PCB,1,1,
SW20,SW_Cherry_MX_1.00u_PCB,1,R,
SW21,SW_Cherry_MX_1.00u_PCB,1,T,
SW22,SW_Cherry_MX_1.00u_PCB,1,Y,
SW23,SW_Cherry_MX_1.00u_PCB,1,U,
SW24,SW_Cherry_MX_1.00u_PCB,1,I,
SW25,SW_Cherry_MX_1.00u_PCB,1,O,
SW26,SW_Cherry_MX_1.00u_PCB,1,P,
SW27,SW_Cherry_MX_1.00u_PCB,1,[,
SW28,SW_Cherry_MX_1.00u_PCB,1,],
SW29,SW_Cherry_MX_1.50u_PCB,1,\,
SW3,SW_Cherry_MX_1.00u_PCB,1,2,
SW30,SW_Cherry_MX_1.00u_PCB,1,INSERT,
SW31,SW_Cherry_MX_1.75u_PCB,1,CAPS LOCK,
SW32,SW_Cherry_MX_1.00u_PCB,1,A,
SW33,SW_Cherry_MX_1.00u_PCB,1,S,
SW34,SW_Cherry_MX_1.00u_PCB,1,D,
SW35,SW_Cherry_MX_1.00u_PCB,1,F,
SW36,SW_Cherry_MX_1.00u_PCB,1,G,
SW37,SW_Cherry_MX_1.00u_PCB,1,H,
SW38,SW_Cherry_MX_1.00u_PCB,1,J,
SW39,SW_Cherry_MX_1.00u_PCB,1,K,
SW4,SW_Cherry_MX_1.00u_PCB,1,3,
SW40,SW_Cherry_MX_1.00u_PCB,1,L,
"SW41, SW49",SW_Cherry_MX_2.25u_PCB,2,SHIFT,
SW42,SW_Cherry_MX_1.00u_PCB,1,;,
SW43,SW_Cherry_MX_1.00u_PCB,1,',
SW44,SW_Cherry_MX_2.25u_PCB,1,ENTER,
SW45,SW_Cherry_MX_1.00u_PCB,1,DELETE,
SW46,SW_Cherry_MX_1.00u_PCB,1,Z,
SW47,SW_Cherry_MX_1.00u_PCB,1,X,
SW48,SW_Cherry_MX_1.00u_PCB,1,C,
SW5,SW_Cherry_MX_1.00u_PCB,1,4,
SW50,SW_Cherry_MX_1.00u_PCB,1,V,
SW51,SW_Cherry_MX_1.00u_PCB,1,B,
SW52,SW_Cherry_MX_1.00u_PCB,1,N,
SW53,SW_Cherry_MX_1.00u_PCB,1,M,
SW54,SW_Cherry_MX_1.00u_PCB,1,",",
SW55,SW_Cherry_MX_1.00u_PCB,1,.,
SW56,SW_Cherry_MX_1.00u_PCB,1,/,
SW57,SW_Cherry_MX_1.00u_PCB,1,UP ARROW,
"SW58, SW66",SW_Cherry_MX_1.25u_PCB,2,CTRL,
"SW59, SW67",SW_Cherry_MX_1.25u_PCB,2,ALT,
SW6,SW_Cherry_MX_1.00u_PCB,1,5,
SW60,SW_Cherry_MX_1.00u_PCB,1,MENU,
SW61,SW_Cherry_MX_6.25u_PCB,1,SPACE,
SW62,SW_Cherry_MX_1.25u_PCB,1,FN,
SW63,SW_Cherry_MX_1.00u_PCB,1,LEFT ARROW,
SW64,SW_Cherry_MX_1.00u_PCB,1,DOWN ARROW,
SW65,SW_Cherry_MX_1.00u_PCB,1,RIGHT ARROW,
SW68,SW_400MSP1R6BLKM6QE,1,POWER,
SW69,SW_DIP_SPSTx08_Slide_9.78x22.5mm_W7.62mm_P2.54mm,1,IO ENABLE,
SW7,SW_Cherry_MX_1.00u_PCB,1,6,
SW70,SW_PUSH_6mm,1,RESET,
SW8,SW_Cherry_MX_1.00u_PCB,1,7,
SW9,SW_Cherry_MX_1.00u_PCB,1,8,
TP1,TestPoint_Pad_2.5x2.5mm,1,VCC,
TP2,TestPoint_Pad_2.5x2.5mm,1,GND,
U1,DIP-40_W15.24mm_Socket_LongPads,1,65C02,
U10,DIP-24_W7.62mm_Socket_LongPads,1,MAX238xNG+,
"U11, U12, U13, U14, U16",DIP-14_W7.62mm_Socket_LongPads,5,74HC00,
U15,DIP-32_W15.24mm_Socket_LongPads,1,AS6C4008,
U17,DIP-14_W7.62mm_Socket_LongPads,1,74HC30,
U18,DIP-28_W15.24mm_Socket_LongPads,1,DS1511Y,
"U19, U20",DIP-16_W7.62mm_Socket_LongPads,2,74HC138,
U2,DIP-40_W15.24mm_Socket_LongPads,1,65C22,
"U21, U22",DIP-20_W7.62mm_Socket_LongPads,2,74HC573,
U3,DIP-40_W15.24mm_Socket_LongPads,1,Pico9918A,
U4,DIP-28_W15.24mm_Socket_LongPads,1,65C51,
U5,DIP-16_W7.62mm_Socket_LongPads,1,74HC163,
U6,DIP-40_W15.24mm_Socket_LongPads,1,ATmega1284-P,
U7,DIP-28_W15.24mm_Socket_LongPads,1,AS6C62256,
U8,DIP_Socket-28_W11.9mm_W12.7mm_W15.24mm_W17.78mm_W18.5mm_3M_228-1277-00-0602J,1,AT28C256,
U9,DIP-28_W15.24mm_Socket_LongPads,1,6581,
X1,Oscillator_DIP-14,1,16MHz,
Y1,Crystal_HC49-U_Vertical,1,1.8432 Mhz,

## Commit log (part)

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2026-04-29 Remove .bak
2026-04-29 Add .bak to gitignore
2026-04-29 Update PDF
2026-04-29 Finish Schematic
2026-04-30 Working on PCB
2026-04-30 Change headers
2026-05-01 Finish PCB layout
2026-05-05 Update ACE project structure
2026-05-05 README fix
2026-05-06 Updates to PCB
2026-05-07 Add CF Adapter
2026-05-11 Change storage header
2026-05-14 Finish ACE Board PCB
2026-05-14 Fix ACE Board images
2026-05-16 Add Base and Top CAD
2026-05-16 Add BOMs
2026-05-17 Add Reset Button and VGA Adapter CAD
2026-05-19 Finish BOM and add to README
2026-05-19 Update BOM
2026-05-19 Add Keyboard Helper jig
2026-05-28 Silkscreen fix
2026-05-30 Update AB Controller firmware
2026-05-30 Ensure SQW input waits for 6502 system boot
2026-05-31 Change some pullup resistor values
2026-05-31 Update AB Controller firmware to disable SQW by default
2026-06-01 Add Rev 1.1
2026-06-01 Update ACE Board Top for RTC IC
2026-06-01 Update ACE Board Top for Pico9918 and ARMSID
2026-06-15 Add bulk capacitance to Rev 1.1
2026-06-15 Add ACE photo
2026-06-16 Remove BOM CSV's
2026-06-18 Ensure accurate Rev 1.0
2026-06-21 README fixes
2026-06-21 Add ACE RAM Patch board
